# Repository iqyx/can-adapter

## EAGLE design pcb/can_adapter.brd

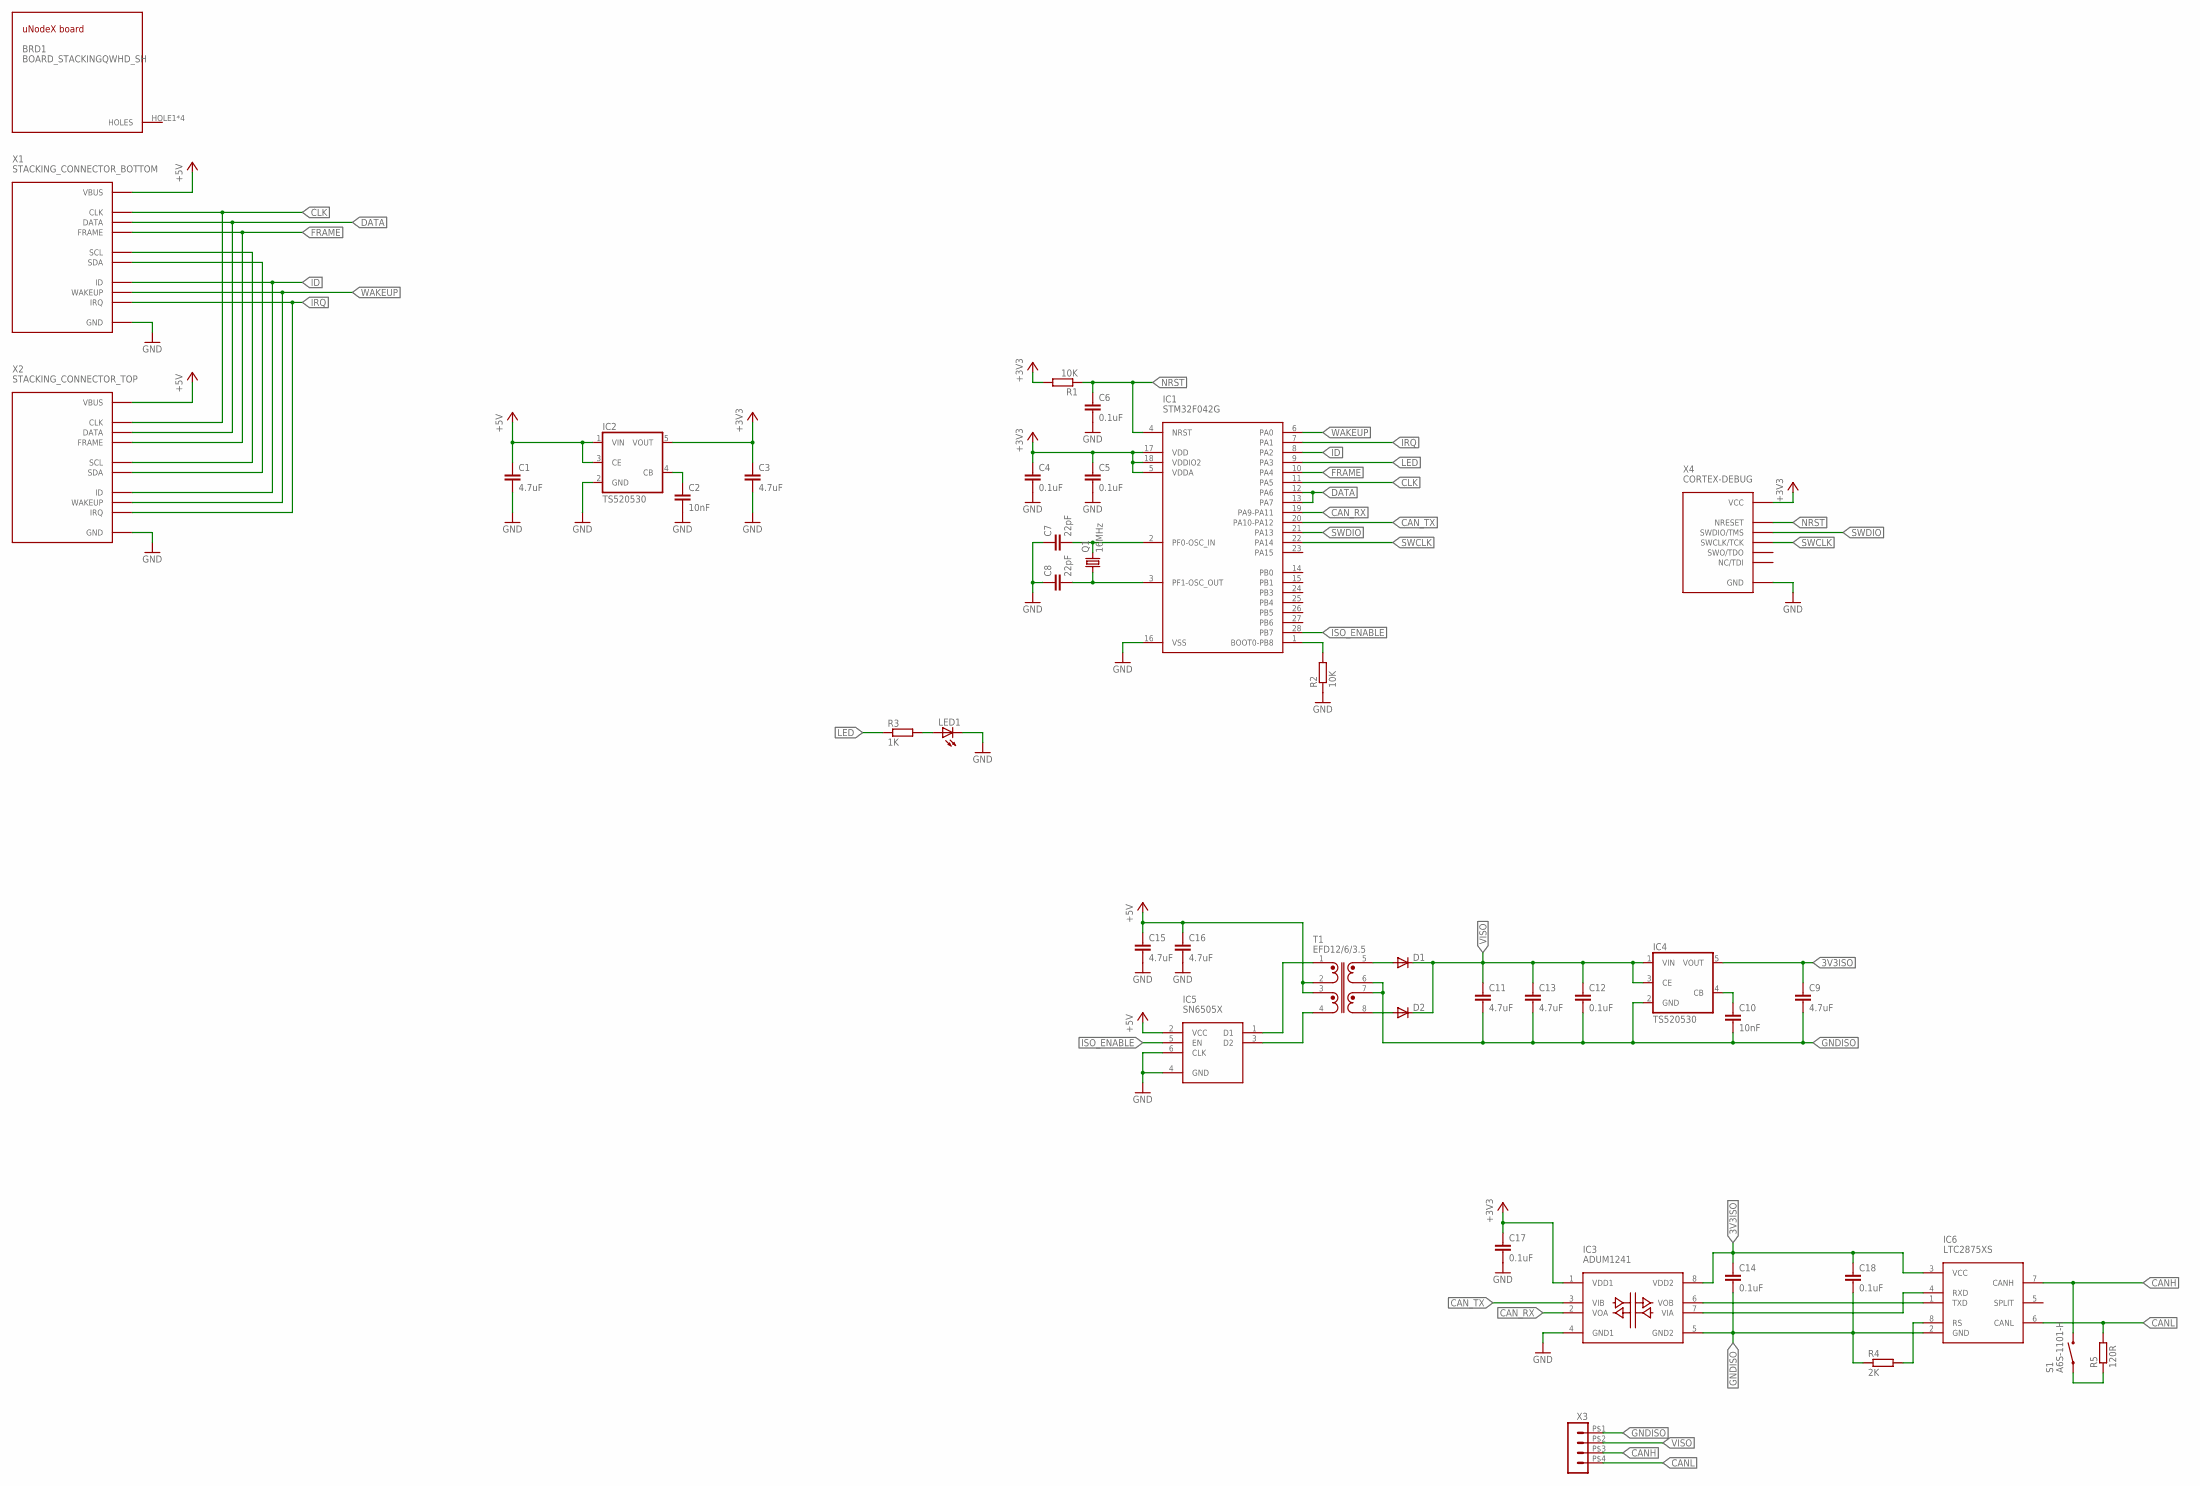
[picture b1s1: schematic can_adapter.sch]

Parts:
BRD1: BOARD_STACKINGQWHD_SH; QWHD_SHARP_CORNERS
C1, C3, C9: 4.7uF; C0805
C2, C10: 10nF; C0603
C4, C5, C6, C12, C14, C17, C18: 0.1uF; C0603
C7, C8: 22pF; C0603
C11, C13, C15, C16: 4.7uF; C1206
D1, D2: DIODE-SOD323-W; SOD323-W
IC1: STM32F042G; UFQFPN28
IC2, IC4: TS520530; SOT25
IC3: ADUM1241; SOIC8
IC5: SN6505X; SOT23-6
IC6: LTC2875XS; SOIC8
LED1: LEDCHIPLED_0805; CHIPLED_0805
Q1: 16MHz; XTAL_3225
R1, R2: 10K; R0603
R3: 1K; R0603
R4: 2K; R0603
R5: 120R; R0603
S1: A6S-1101-H; A6S-1
T1: EFD12/6/3.5
X1: STACKING_CONNECTOR_BOTTOM; HAR-FLEX-BOTTOM-12P
X2: STACKING_CONNECTOR_TOP; HAR-FLEX-TOP-12P
X3: HEADER_POS4_43650-0400; 43650-0400
X4: CORTEX-DEBUG

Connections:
3V3ISO: C9.1, C14.1, C18.1, IC3.8 (VDD2), IC4.5 (VOUT), IC6.3 (VCC)
+3V3: C3.1, C4.1, C5.1, C17.1, IC1.5 (VDDA), IC1.17 (VDD), IC1.18 (VDDIO2), IC2.5 (VOUT), IC3.1 (VDD1), R1.2, X4.VCC
+5V: C1.1, C15.1, C16.1, IC2.1 (VIN), IC2.3 (CE), IC5.2 (VCC), T1.2, T1.3, X1.VBUS, X2.VBUS
CANH: IC6.7 (CANH), S1.1B (B), X3.P$3 (3)
CANL: IC6.6 (CANL), R5.2, X3.P$4 (4)
CAN_RX: IC1.19 (PA9-PA11), IC3.2 (VOA)
CAN_TX: IC1.20 (PA10-PA12), IC3.3 (VIB)
CLK: IC1.11 (PA5), X1.CLK, X2.CLK
DATA: IC1.12 (PA6), IC1.13 (PA7), X1.DATA, X2.DATA
FRAME: IC1.10 (PA4), X1.FRAME, X2.FRAME
GND: C1.2, C2.2, C3.2, C4.2, C5.2, C6.2, C7.1, C8.1, C15.2, C16.2, C17.2, IC1.16 (VSS), IC2.2 (GND), IC3.4 (GND1), IC5.4 (GND), IC5.6 (CLK), LED1.C, R2.1, X1.GND1 (GND), X1.GND2 (GND), X1.GND3 (GND), X1.H1 (GND), X1.H2 (GND), X1.H3 (GND), X1.H4 (GND), X2.GND1 (GND), X2.GND2 (GND), X2.GND3 (GND), X2.H1 (GND), X2.H2 (GND), X2.H3 (GND), X2.H4 (GND), X4.GND1 (GND), X4.GND2 (GND), X4.GND_DETECT (GND)
GNDISO: C9.2, C10.2, C11.2, C12.2, C13.2, C14.2, C18.2, IC3.5 (GND2), IC4.2 (GND), IC6.2 (GND), R4.1, T1.6, T1.7, X3.P$1 (1)
ID: IC1.8 (PA2), X1.ID, X2.ID
IRQ: IC1.7 (PA1), X1.IRQ, X2.IRQ
ISO_ENABLE: IC1.28 (PB7), IC5.5 (EN)
LED: IC1.9 (PA3), R3.1
unnamed: IC5.3 (D2), T1.4
unnamed: LED1.A, R3.2
unnamed: IC3.6 (VOB), IC6.1 (TXD)
unnamed: IC3.7 (VIA), IC6.4 (RXD)
unnamed: IC6.8 (RS), R4.2
unnamed: R5.1, S1.1A (A)
unnamed: C7.2, IC1.2 (PF0-OSC_IN), Q1.3 (2)
unnamed: C8.2, IC1.3 (PF1-OSC_OUT), Q1.1
unnamed: IC1.1 (BOOT0-PB8), R2.2
unnamed: C10.1, IC4.4 (CB)
unnamed: IC5.1 (D1), T1.1
unnamed: D1.A, T1.5
unnamed: D2.A, T1.8
unnamed: C2.1, IC2.4 (CB)
NRST: C6.1, IC1.4 (NRST), R1.1, X4.NRESET
SCL: X1.SCL, X2.SCL
SDA: X1.SDA, X2.SDA
SWCLK: IC1.22 (PA14), X4.SWCLK/TCK
SWDIO: IC1.21 (PA13), X4.SWDIO/TMS
VISO: C11.1, C12.1, C13.1, D1.C, D2.C, IC4.1 (VIN), IC4.3 (CE), X3.P$2 (2)
WAKEUP: IC1.6 (PA0), X1.WAKEUP, X2.WAKEUP

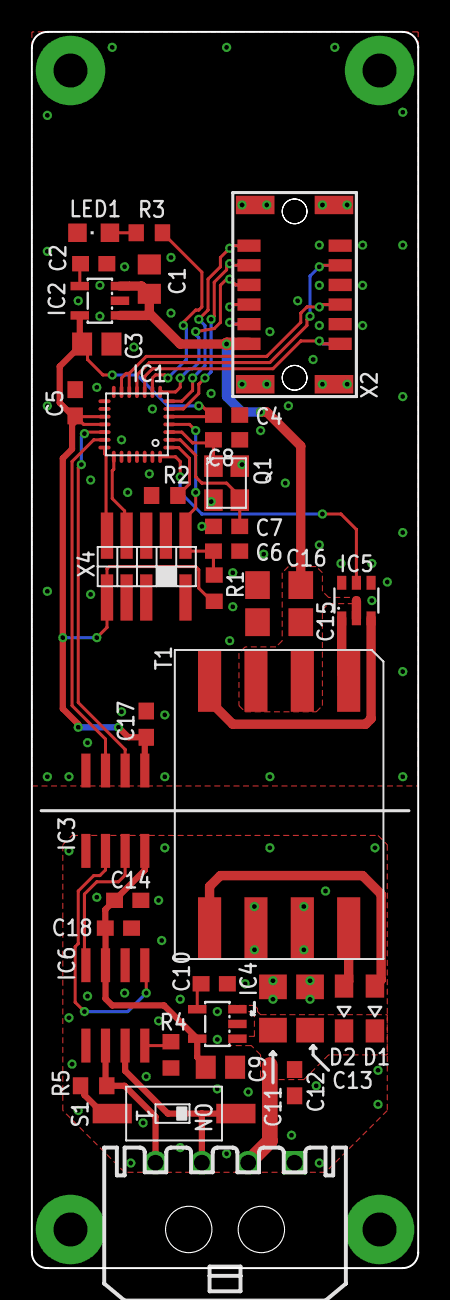
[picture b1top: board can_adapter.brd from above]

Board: 2 copper layers, 25.0 x 80.0 mm, 40 parts (0 on the bottom side), 37 nets.

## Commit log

2017-12-08 Add libopencm3 and nanopb submodules
2017-12-08 Add a basic firmware which reads all received messages using the UXB bus
2017-12-08 Add schematic and layout files (Eagle)
2017-12-08 Add gerber exports (seeedstudio compatible)

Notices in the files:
pcb/can_adapter.brd:
(c) 2017 qyx@krtko.org, CC-BY-SA
